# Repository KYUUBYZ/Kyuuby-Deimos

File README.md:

<!--START_SECTION:BOM-TABLE-->
| Item | Qty | Supplier | Cost/item | Total Cost | link |
| --- | --- | --- | --- | --- | --- |
| 100nF | 11 | Unikeyic | $0.01 | $0.11 | [Link](https://www.unikeyic.com/products/ceramic-capacitors/0805b104k250ct/6132896.html?sku=1003001022740982) |
| 2.2uF | 2 | Unikeyic | $0.03 | $0.06 | [Link](https://www.unikeyic.com/products/ceramic-capacitors/cga4j3x7r1c225kt0y0n/8873476.html?sku=1003001017784221) |
| 1uF | 1 | Unikeyic | $0.03 | $0.03 | [Link](https://www.unikeyic.com/products/ceramic-capacitors/c0805c105j8nac7800/7749019.html?sku=1003001430122656) |
| 4.7uF | 1 | Unikeyic | $0.02 | $0.02 | [Link](https://www.unikeyic.com/products/ceramic-capacitors/0805f475z160ct/21004299.html?sku=1003001428770251) |
| 10uF | 2 | Unikeyic | $0.02 | $0.04 | [Link](https://www.unikeyic.com/products/ceramic-capacitors/tcc0805x5r106k250ft/29556797.html?sku=1003001012423182) |
| 33pF | 2 | Unikeyic | $0.04 | $0.08 | [Link](https://www.unikeyic.com/products/ceramic-capacitors/cc0805frnpo9bn330/19420111.html?sku=1003001013968419) |
| 10nF | 2 | Unikeyic | $0.01 | $0.02 | [Link](https://www.unikeyic.com/products/ceramic-capacitors/cc0805jrx7r9bb103/17962920.html?sku=1003001445184833) |
| 470nF | 1 | Unikeyic | $0.01 | $0.01 | [Link](https://www.unikeyic.com/products/ceramic-capacitors/0805b474k250nt/19037919.html?sku=1003001014882301) |
| 100pF | 1 | Unikeyic | $0.01 | $0.01 | [Link](https://www.unikeyic.com/products/ceramic-capacitors/0805b101k500nt/7374829.html?sku=1003001014881895) |
| 0.5pF | 1 | Unikeyic | $0.02 | $0.02 | [Link](https://www.unikeyic.com/products/ceramic-capacitors/cc0805crnpo9bnr50/7291562.html?sku=100300109292912) |
| 600R | 1 | Unikeyic | $0.01 | $0.01 | [Link](https://www.unikeyic.com/products/magnetic-beads/blm18ag601sn1d/23500677.html?sku=1003001442987065) |
| SX1280IMLTRT | 1 | Unikeyic | $4.19 | $4.19 | [Link](https://www.unikeyic.com/products/wireless-transceiver/sx1280imltrt/10812057.html?sku=1003001031598558) |
| USB_C_Receptacle_USB2.0_16P | 1 | Unikeyic | $0.06 | $0.06 | [Link](https://www.unikeyic.com/products/usb-dvi-hdmi-connectors/type-c-16pin-2md-073/22541599.html?sku=1003001021518676) |
| 15uH | 1 | Unikeyic | $0.03 | $0.03 | [Link](https://www.unikeyic.com/products/chip-inductor/mlz2012m150wt000/23579160.html?sku=1003001444225920) |
| 10k | 4 | Unikeyic | $0.00 | $0.00 | [Link](https://www.unikeyic.com/products/surface-mount-resistors/rtt051002ftp/8868151.html?sku=1003001017270744) |
| 5.1k | 2 | Unikeyic | $0.00 | $0.00 | [Link](https://www.unikeyic.com/products/surface-mount-resistors/sc0805j5101f4anrh/691840803.html?sku=1003001042867065) |
| 0R | 1 | Unikeyic | $0.01 | $0.01 | [Link](https://www.unikeyic.com/products/surface-mount-resistors/rtt050000ftp/30082103.html?sku=1003001013772933) |
| 1k | 1 | Unikeyic | $0.00 | $0.00 | [Link](https://www.unikeyic.com/products/surface-mount-resistors/0805w8f1001t5e/1478193.html?sku=1003001012328861) |
| STM32F405RGTx | 1 | LCSC | $6.88 | $6.88 | [Link](https://www.lcsc.com/product-detail/C15742.html) |
| BMI270 | 1 | Unikeyic | $1.12 | $1.12 | [Link](https://www.unikeyic.com/products/accelerometers/bmi270/35035999.html?sku=1003001445188098) |
| W25Q128DR-TD | 1 | LCSC | $2.52 | $2.52 | [Link](https://www.lcsc.com/product-detail/C49211308.html) |
| AP2112K-3.3TRG1 | 1 | Unikeyic | $0.05 | $0.05 | [Link](https://www.unikeyic.com/products/ldo-controller/ap2112k-3-3trg1/35425428.html?sku=1003001026995398) |
| USBLC6-2SC6 | 1 | Unikeyic | $0.03 | $0.03 | [Link](https://www.unikeyic.com/products/esd-suppressors/usblc6-2sc6/14464614.html?sku=1003001443023533) |
| Antenna | 1 | LCSC | $0.37 | $0.37 | [Link](https://www.lcsc.com/product-detail/C19192917.html) |
| 8MHz | 1 | Unikeyic | $0.09 | $0.09 | [Link](https://www.unikeyic.com/products/crystals/xc32m4-8-000-f20njdt/688055058.html?sku=1003001042451847) |
| 52MHz | 1 | LCSC | $0.12 | $0.12 | [Link](https://www.lcsc.com/product-detail/C7294606.html) |
| Estimated total shipping | 1 |  |  | $17.00 |  |
<!--END_SECTION:BOM-TABLE-->

# Kyuuby-Deimos
A normal quadcopter drone's flight controller. this is only the V1, but in the future i will build a better one, becaus this one doesnt have the motor input and output.
It uses an STM32F405 as MCU, wit ha 8MHz crystal as OSC. It uses a SPI3 protocol to communicate with the SX1280 ( the radio module ) and SPI1 protocol for the BMI270, the IMU (Gyroscope and Accelerometer).
Its only purpose for now is to be a test to see if my design can works, so in the firmware there won't be anything difficult.

You will find a "detailed" (hope its detailed enough) guide in /Firmware.

# Schematic: 

# PCB:

# Physical View:

Everything made by me and with the help of internet!

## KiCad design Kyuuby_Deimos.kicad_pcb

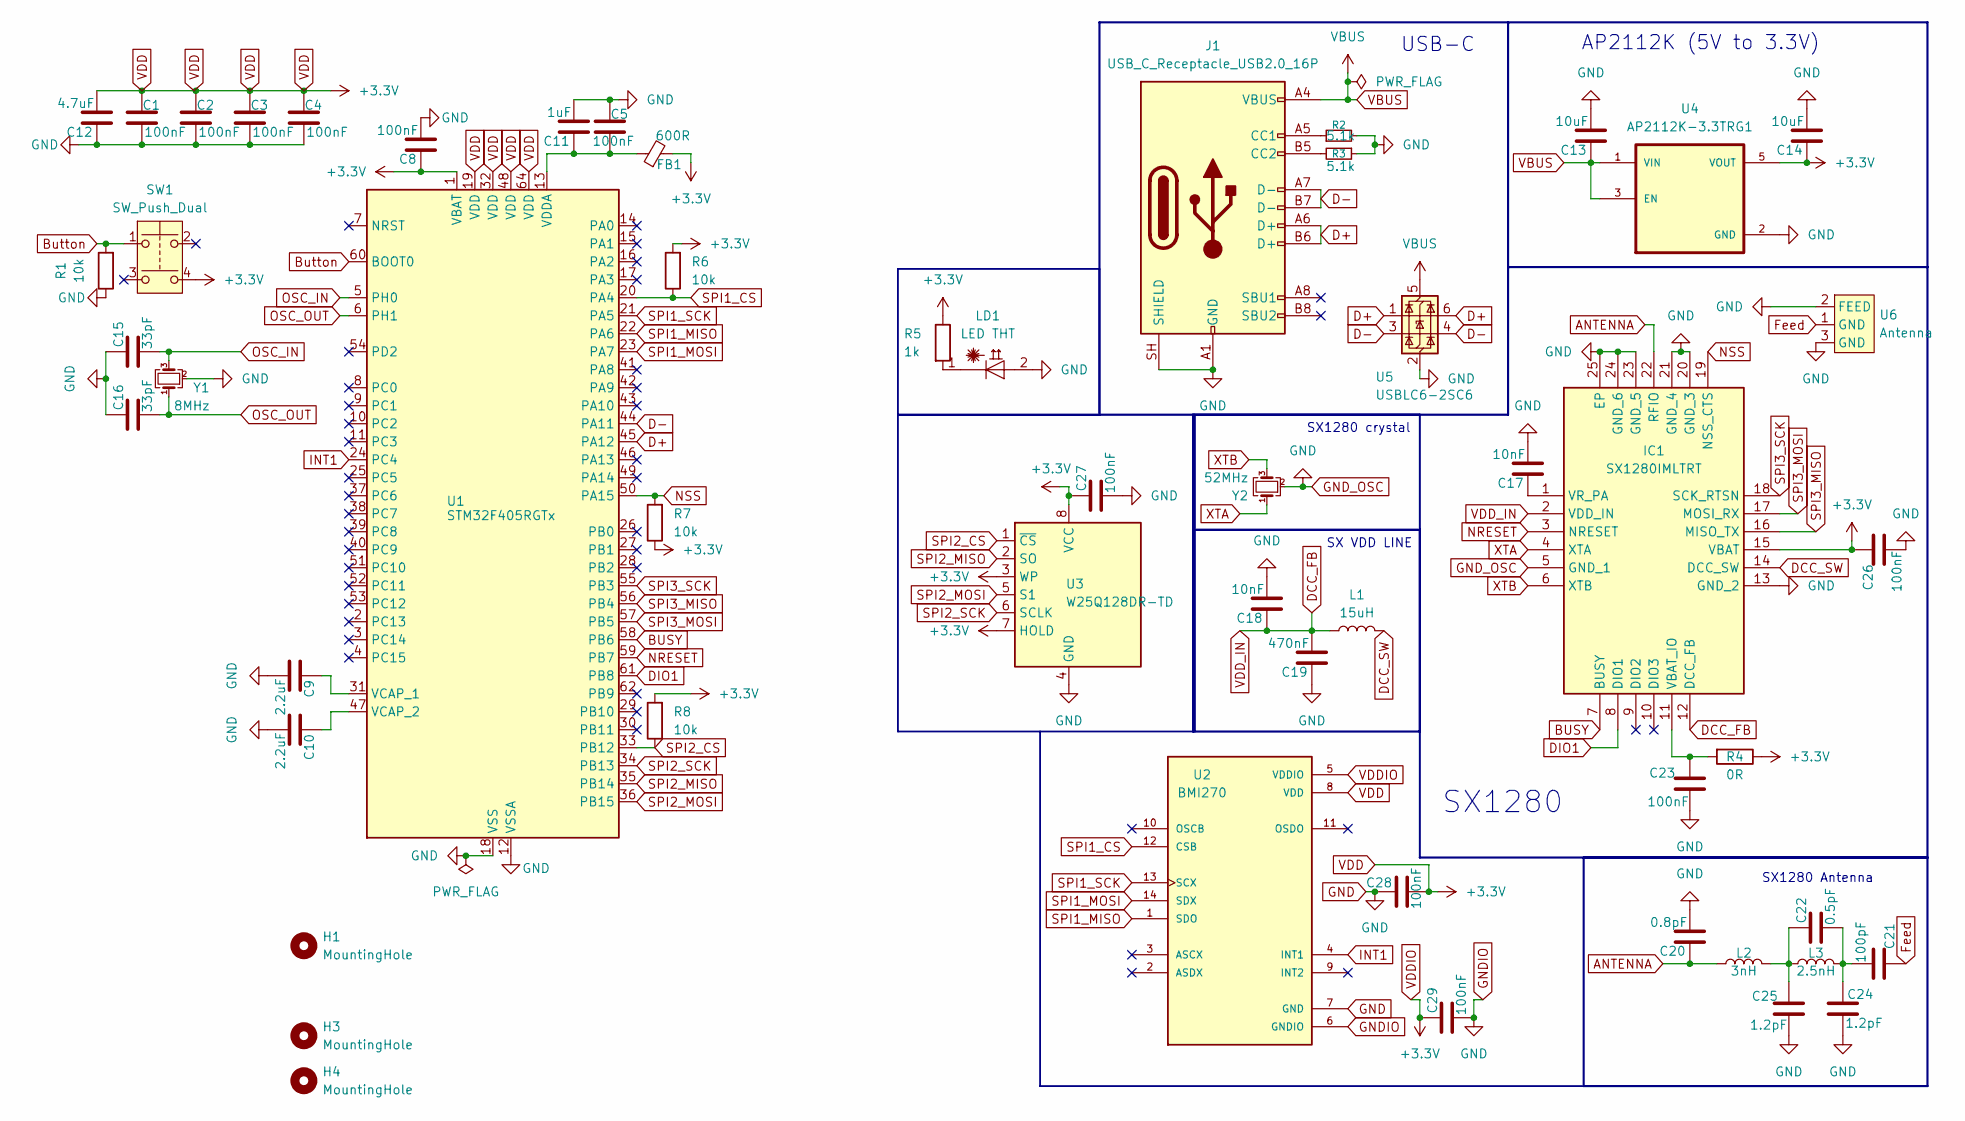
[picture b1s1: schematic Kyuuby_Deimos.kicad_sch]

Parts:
C1, C2, C3, C4, C5, C8, C23, C26, C27, C28, C29: 100nF; C_0805_2012Metric_Pad1.18x1.45mm_HandSolder
C9, C10: 2.2uF; C_0805_2012Metric_Pad1.18x1.45mm_HandSolder
C11: 1uF; C_0805_2012Metric_Pad1.18x1.45mm_HandSolder
C12: 4.7uF; C_0805_2012Metric_Pad1.18x1.45mm_HandSolder
C13, C14: 10uF; C_0805_2012Metric_Pad1.18x1.45mm_HandSolder
C15, C16: 33pF; C_0805_2012Metric_Pad1.18x1.45mm_HandSolder
C17, C18: 10nF; C_0805_2012Metric_Pad1.18x1.45mm_HandSolder
C19: 470nF; C_0805_2012Metric_Pad1.18x1.45mm_HandSolder
C20: 0.8pF; C_0805_2012Metric_Pad1.18x1.45mm_HandSolder
C21: 100pF; C_0805_2012Metric_Pad1.18x1.45mm_HandSolder
C22: 0.5pF; C_0805_2012Metric_Pad1.18x1.45mm_HandSolder
C24, C25: 1.2pF; C_0805_2012Metric_Pad1.18x1.45mm_HandSolder
FB1: 600R; L_0603_1608Metric_Pad1.05x0.95mm_HandSolder
H1, H3, H4: MountingHole; MountingHole_2.5mm
IC1: SX1280IMLTRT; QFN50P400X400X100-25N-D; Manufacturer_Part_Number SX1280IMLTRT
J1: USB_C_Receptacle_USB2.0_16P; USB_C_Receptacle_GCT_USB4105-xx-A_16P_TopMnt_Horizontal
L1: 15uH; L_0805_2012Metric_Pad1.05x1.20mm_HandSolder
L2: 3nH; L_0805_2012Metric_Pad1.05x1.20mm_HandSolder
L3: 2.5nH; L_0805_2012Metric_Pad1.05x1.20mm_HandSolder
LD1: LED THT; LED_D5.0mm
R1, R6, R7, R8: 10k; R_0805_2012Metric_Pad1.20x1.40mm_HandSolder
R2, R3: 5.1k; R_0805_2012Metric_Pad1.20x1.40mm_HandSolder
R4: 0R; R_0805_2012Metric_Pad1.20x1.40mm_HandSolder
R5: 1k; R_0805_2012Metric_Pad1.20x1.40mm_HandSolder
SW1: SW_Push_Dual; Button 5mm-7mm
U1: STM32F405RGTx; LQFP-64_10x10mm_P0.5mm
U2: BMI270; XDCR_BMI270
U3: W25Q128DR-TD; SOIC-8_5.3x5.3mm_P1.27mm
U4: AP2112K-3.3TRG1; SOT95P285X140-5N; PARTREV 2-2
U5: USBLC6-2SC6; SOT-23-6
U6: Antenna; 2.4GHz Antenna
Y1: 8MHz; Crystal_SMD_3225-4Pin_3.2x2.5mm
Y2: 52MHz; Crystal_SMD_3225-4Pin_3.2x2.5mm

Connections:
ANTENNA: C20.1, IC1.22 (RFIO), L2.1
BUSY: IC1.7 (BUSY), U1.58 (PB6)
Button: R1.2, SW1.1, U1.60 (BOOT0)
D+: J1.A6 (D+), J1.B6 (D+), U1.45 (PA12), U5.1 (I/O1), U5.6 (I/O1)
D-: J1.A7 (D-), J1.B7 (D-), U1.44 (PA11), U5.3 (I/O2), U5.4 (I/O2)
DCC_FB: C18.1, C19.2, IC1.2 (VDD_IN), IC1.12 (DCC_FB), L1.1
DCC_SW: IC1.14 (DCC_SW), L1.2
DIO1: IC1.8 (DIO1), U1.61 (PB8)
Feed: C21.1, U6.1 (GND)
GND: C1.2, C2.2, C3.2, C4.2, C5.1, C8.2, C9.2, C10.2, C11.2, C12.1, C13.2, C14.2, C15.1, C16.1, C17.2, C18.2, C19.1, C20.2, C23.2, C24.2, C25.2, C26.2, C27.2, C28.1, C29.2, IC1.5 (GND_1), IC1.13 (GND_2), IC1.20 (GND_3), IC1.21 (GND_4), IC1.23 (GND_5), IC1.24 (GND_6), IC1.25 (EP), J1.A1 (GND), J1.A12 (GND), J1.B1 (GND), J1.B12 (GND), J1.SH (SHIELD), LD1.2 (A), R1.1, R2.2, R3.1, U1.12 (VSSA), U1.18 (VSS), U1.63 (VSS), U2.6 (GNDIO), U2.7 (GND), U3.4 (GND), U4.2 (GND), U5.2 (GND), U6.2 (FEED), U6.3 (GND), Y1.2 (G), Y1.4 (G), Y2.2 (G), Y2.4 (G)
INT1: U1.24 (PC4), U2.4 (INT1)
NRESET: IC1.3 (NRESET), U1.59 (PB7)
NSS: IC1.19 (NSS_CTS), R7.2, U1.50 (PA15)
unnamed: C21.2, C22.2, C24.1, L3.2
unnamed: C22.1, C25.1, L2.2, L3.1
unnamed: C23.1, IC1.11 (VBAT_IO), R4.2
unnamed: C17.1, IC1.1 (VR_PA)
unnamed: J1.A5 (CC1), R2.1
unnamed: J1.B5 (CC2), R3.2
unnamed: LD1.1 (C), R5.2
unnamed: C9.1, U1.31 (VCAP_1)
unnamed: C10.1, U1.47 (VCAP_2)
unnamed: C5.2, C11.1, FB1.1, U1.13 (VDDA)
OSC_IN: C15.2, U1.5 (PH0), Y1.3
OSC_OUT: C16.2, U1.6 (PH1), Y1.1
SPI1_CS: R6.1, U1.20 (PA4), U2.12 (CSB)
SPI1_MISO: U1.22 (PA6), U2.1 (SDO)
SPI1_MOSI: U1.23 (PA7), U2.14 (SDX)
SPI1_SCK: U1.21 (PA5), U2.13 (SCX)
SPI2_CS: R8.1, U1.33 (PB12), U3.1 (~CS)
SPI2_MISO: U1.35 (PB14), U3.2 (SO)
SPI2_MOSI: U1.36 (PB15), U3.5 (S1)
SPI2_SCK: U1.34 (PB13), U3.6 (SCLK)
SPI3_MISO: IC1.16 (MISO_TX), U1.56 (PB4)
SPI3_MOSI: IC1.17 (MOSI_RX), U1.57 (PB5)
SPI3_SCK: IC1.18 (SCK_RTSN), U1.55 (PB3)
VBUS: C13.1, J1.A4 (VBUS), J1.A9 (VBUS), J1.B4 (VBUS), J1.B9 (VBUS), U4.1 (VIN), U4.3 (EN), U5.5 (VBUS)
VDD: C1.1, C2.1, C3.1, C4.1, C8.1, C12.2, C14.1, C26.1, C27.1, C28.2, C29.1, FB1.2, IC1.15 (VBAT), R4.1, R5.1, R6.2, R7.1, R8.2, SW1.4, U1.1 (VBAT), U1.19 (VDD), U1.32 (VDD), U1.48 (VDD), U1.64 (VDD), U2.5 (VDDIO), U2.8 (VDD), U3.3 (WP), U3.7 (HOLD), U3.8 (VCC), U4.5 (VOUT)
XTA: IC1.4 (XTA), Y2.1
XTB: IC1.6 (XTB), Y2.3

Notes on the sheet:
USB-C
SX1280 crystal
SX1280
SX1280 Antenna
SX VDD LINE
AP2112K (5V to 3.3V)

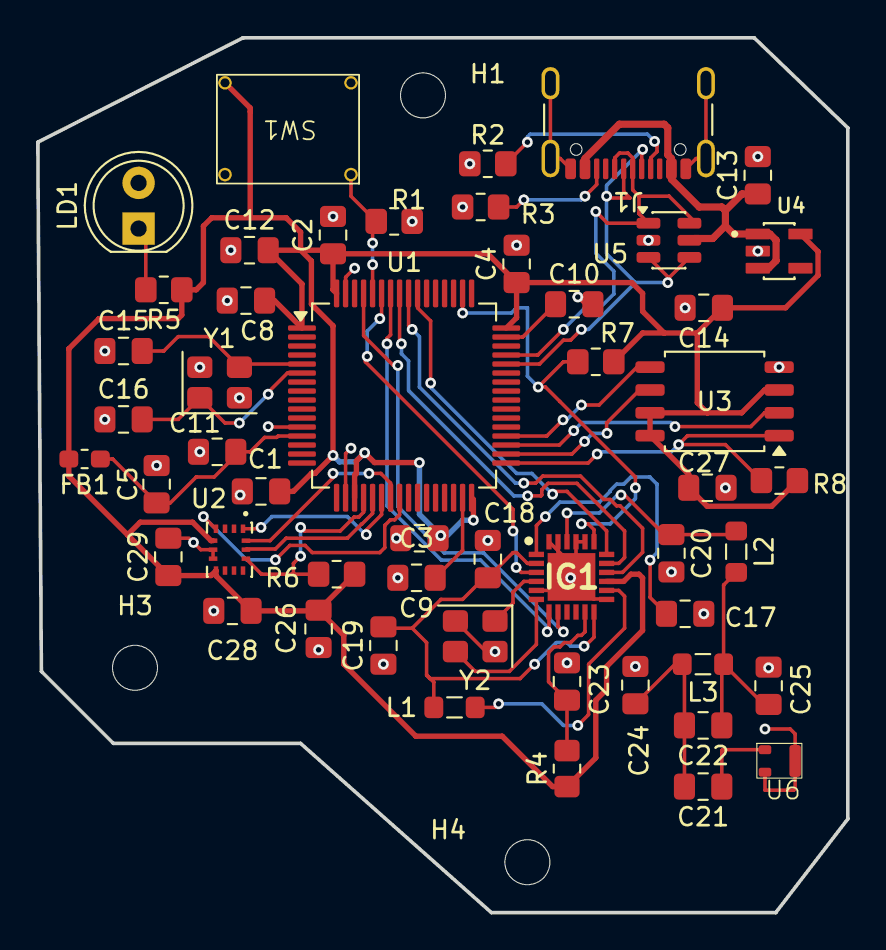
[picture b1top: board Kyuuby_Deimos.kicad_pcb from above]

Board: 2 copper layers, 45.0 x 48.6 mm, 54 parts (0 on the bottom side), 40 nets.

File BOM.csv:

Item,Qty,Supplier,Cost/item,Total Cost,link
100nF,11,Unikeyic,$0.01,$0.11,https://www.unikeyic.com/products/ceramic-capacitors/0805b10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
2.2uF,2,Unikeyic,$0.03,$0.06,https://www.unikeyic.com/products/ceramic-capacitors/cga4j3x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
1uF,1,Unikeyic,$0.03,$0.03,https://www.unikeyic.com/products/ceramic-capacitors/c0805c1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
4.7uF,1,Unikeyic,$0.02,$0.02,https://www.unikeyic.com/products/ceramic-capacitors/0805f47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
10uF,2,Unikeyic,$0.02,$0.04,https://www.unikeyic.com/products/ceramic-capacitors/tcc0805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
33pF,2,Unikeyic,$0.04,$0.08,https://www.unikeyic.com/products/ceramic-capacitors/cc0805f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
10nF,2,Unikeyic,$0.01,$0.02,https://www.unikeyic.com/products/ceramic-capacitors/cc0805j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
470nF,1,Unikeyic,$0.01,$0.01,https://www.unikeyic.com/products/ceramic-capacitors/0805b47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
100pF,1,Unikeyic,$0.01,$0.01,https://www.unikeyic.com/products/ceramic-capacitors/0805b10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
0.5pF,1,Unikeyic,$0.02,$0.02,https://www.unikeyic.com/products/ceramic-capacitors/cc0805c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
600R,1,Unikeyic,$0.01,$0.01,https://www.unikeyic.com/products/magnetic-beads/blm18ag601s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
SX1280IMLTRT,1,Unikeyic,$4.19,$4.19,https://www.unikeyic.com/products/wireless-transceiver/sx128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
USB_C_Receptacle_USB2.0_16P,1,Unikeyic,$0.06,$0.06,https://www.unikeyic.com/products/usb-dvi-hdmi-connectors/ty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
15uH,1,Unikeyic,$0.03,$0.03,https://www.unikeyic.com/products/chip-inductor/mlz2012m150w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
10k,4,Unikeyic,$0.00,$0.00,https://www.unikeyic.com/products/surface-mount-resistors/rt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
5.1k,2,Unikeyic,$0.00,$0.00,https://www.unikeyic.com/products/surface-mount-resistors/sc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
0R,1,Unikeyic,$0.01,$0.01,https://www.unikeyic.com/products/surface-mount-resistors/rt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
1k,1,Unikeyic,$0.00,$0.00,https://www.unikeyic.com/products/surface-mount-resistors/08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
STM32F405RGTx,1,LCSC,$6.88,$6.88,https://www.lcsc.com/product-detail/C15742.html
BMI270,1,Unikeyic,$1.12,$1.12,https://www.unikeyic.com/products/accelerometers/bmi270/3503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
W25Q128DR-TD,1,LCSC,$2.52,$2.52,https://www.lcsc.com/product-detail/C49211308.html
AP2112K-3.3TRG1,1,Unikeyic,$0.05,$0.05,https://www.unikeyic.com/products/ldo-controller/ap2112k-3-3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
USBLC6-2SC6,1,Unikeyic,$0.03,$0.03,https://www.unikeyic.com/products/esd-suppressors/usblc6-2sc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
Antenna,1,LCSC,$0.37,$0.37,https://www.lcsc.com/product-detail/C19192917.html
8MHz,1,Unikeyic,$0.09,$0.09,https://www.unikeyic.com/products/crystals/xc32m4-8-000-f20n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
52MHz,1,LCSC,$0.12,$0.12,https://www.lcsc.com/product-detail/C7294606.html
Estimated total shipping,1,,,$17.00,

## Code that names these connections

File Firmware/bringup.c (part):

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 *   [RADIO] SX1280 su SPI3: reset con NRESET, BUSY, GetStatus, registro versione firmware
 *
 * Pin usati (dallo schema):
 *   SPI1 IMU   : PA5 SCK, PA6 MISO, PA7 MOSI, PA4 CS,  PC4 INT1
 *   SPI2 flash : PB13 SCK, PB14 MISO, PB15 MOSI, PB12 CS
 *   SPI3 radio : PB3 SCK, PB4 MISO, PB5 MOSI, PA15 NSS, PB7 NRESET, PB6 BUSY, PB8 DIO1
 *
 * Dipende solo da: CMSIS (registri), HAL_GetTick/HAL_Delay, e dallo stack USB CDC
 * generato da CubeMX (CDC_Transmit_FS, hUsbDeviceFS).
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    gpio_cfg(RF_DIO1_PORT, RF_DIO1_PIN, BU_IN, 0);
    gpio_cfg(IMU_INT_PORT, IMU_INT_PIN, BU_IN, 0);

    /* SPI1: PA5 SCK, PA6 MISO, PA7 MOSI -> AF5 */
    gpio_cfg(GPIOA, 5,  BU_AF, 5);
    gpio_cfg(GPIOA, 6,  BU_AF, 5);
    gpio_cfg(GPIOA, 7,  BU_AF, 5);
    /* SPI2: PB13 SCK, PB14 MISO, PB15 MOSI -> AF5 */
    gpio_cfg(GPIOB, 13, BU_AF, 5);
    gpio_cfg(GPIOB, 14, BU_AF, 5);
    gpio_cfg(GPIOB, 15, BU_AF, 5);
    /* SPI3: PB3 SCK, PB4 MISO, PB5 MOSI -> AF6 (sovrascrive la funzione JTAG di reset) */
    gpio_cfg(GPIOB, 3,  BU_AF, 6);
    gpio_cfg(GPIOB, 4,  BU_AF, 6);
    gpio_cfg(GPIOB, 5,  BU_AF, 6);
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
